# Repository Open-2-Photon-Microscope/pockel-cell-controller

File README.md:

# Pockel cell controller

An open source circuit to modulate laser intensity in a 2 Photon microscope. This modulation is necessary when visual stimulation is used to elicit responses from biological tissue (photoreceptors). The laser power is tunned high and low periodically (in our systems at 500Hz using a square wavefom at 80% duty cycle). When laser power is low, visual stimulation is on, when laser power is high, visual stimulation is off. 

This driver was built to control a laser modulator from Conoptics. Specifically [his model](https://www.lambdaphoto.co.uk/electro-optic-modulator-systems.html).

The main purpose of this circuit is to condition an analog signal using an fast switch IC that opens and closes the analog line using a digital 0-5V square signal (0V circuit open, 5V circuit closed). The original switching signal is 1.6ms at 5V and 0.4ms at 0V (composing a 500Hz signal), but other signals can be used.

This board can take an internal analog signal, where the signal amplitude (and therefore the laser intensity) is set by a potentiometer, or an external signal connected via a BNC cable.
 
The Pockels' cell driver was inspired by earlier devices designed and built by R. Berndt ([HIH Tübingen](<https://www.hih-tuebingen.de/en/>)), part of a project of [T. Euler's lab](<http://www.eye-tuebingen.de/eulerlab/>).

## To do:
1. Link board to KitSpace

## History:

v2.0
- Document, add licenses to the repository (A. Maia Chagas)
- KiCad designs updated to KiCad 5 (A. Maia Chagas)
- Designs of the board updated; ported to KiCad (F. Janiak)

V1.0
 - Pockels' cell driver design by R. Berndt ([HIH Tübingen](<https://www.hih-tuebingen.de/en/>)) and [T. Euler's lab](<http://www.eye-tuebingen.de/eulerlab/>).

--- 

Footprints for KiCad downloaded from [ultralibrarian](<https://app.ultralibrarian.com>).

- [CA3240](<https://app.ultralibrarian.com/details/f0fe15b2-106c-11e9-ab3a-0a3560a4cccc/Intersil/CA3240AE?uid=155cdc561030ca9b&exports=KiCAD>)
- [LM10CLN](<https://app.ultralibrarian.com/details/49f2f7e6-1073-11e9-ab3a-0a3560a4cccc/Texas-Instruments/LM10CLN?uid=6d97a49d38e0b250&exports=KiCAD>)

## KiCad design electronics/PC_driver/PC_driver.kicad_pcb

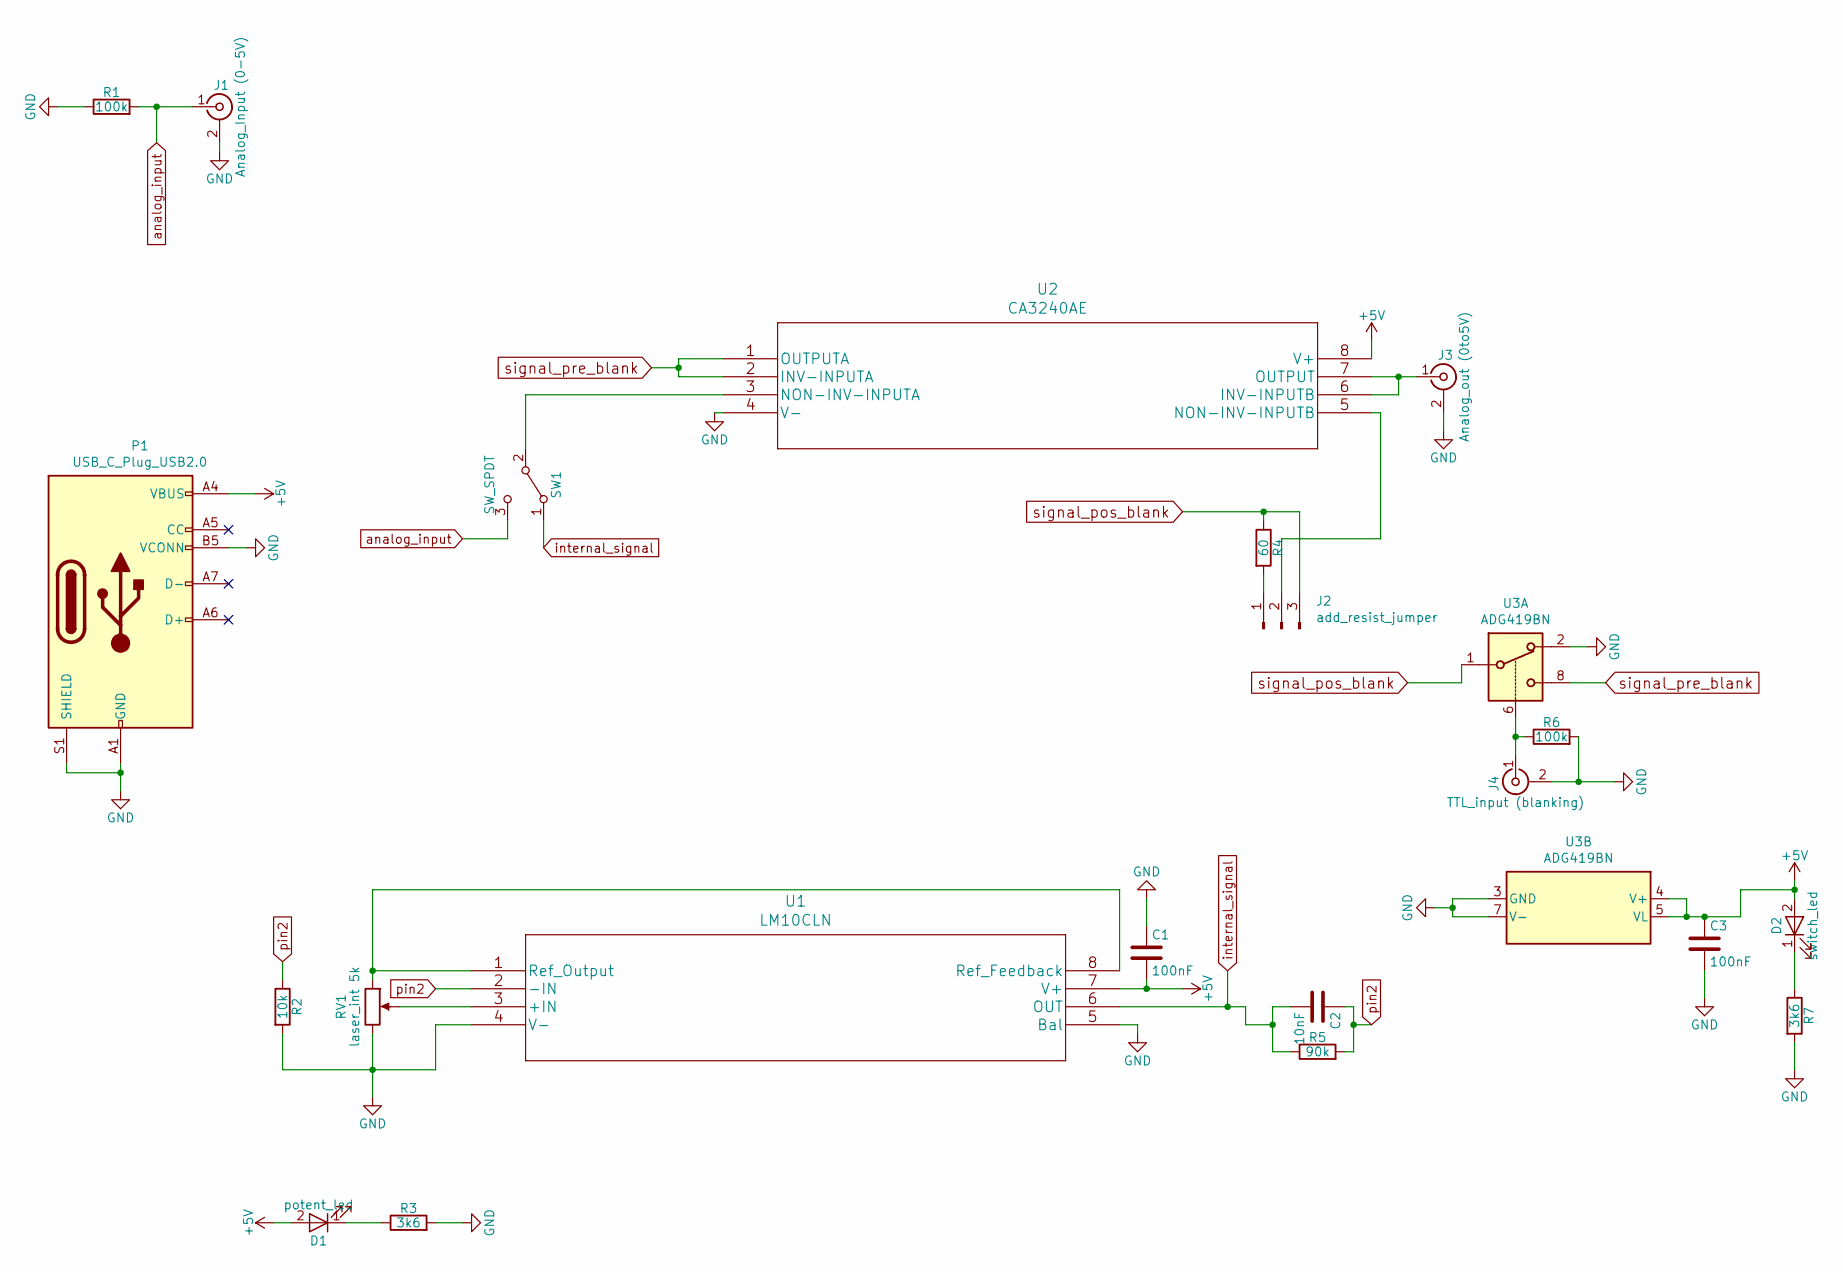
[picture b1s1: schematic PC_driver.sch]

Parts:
C1, C3: 100nF; C_Disc_D5.0mm_W2.5mm_P2.50mm
C2: 10nF; C_Disc_D5.0mm_W2.5mm_P2.50mm
D1: potent_led; LED_D5.0mm_Clear
D2: switch_led; LED_D5.0mm_Clear
J1: Analog_Input (0-5V); BNC_Amphenol_B6252HB-NPP3G-50_Horizontal
J2: add_resist_jumper; PinHeader_1x03_P2.54mm_Vertical
J3: Analog_out (0to5V); BNC_Amphenol_B6252HB-NPP3G-50_Horizontal
J4: TTL_input (blanking); BNC_Amphenol_B6252HB-NPP3G-50_Horizontal
P1: USB_C_Plug_USB2.0; USB_C_Receptacle_GCT_USB4085
R1, R6: 100k; R_Axial_DIN0309_L9.0mm_D3.2mm_P12.70mm_Horizontal
R2: 10k; R_Axial_DIN0309_L9.0mm_D3.2mm_P12.70mm_Horizontal
R3, R7: 3k6; R_Axial_DIN0309_L9.0mm_D3.2mm_P12.70mm_Horizontal
R4: 60; R_Axial_DIN0309_L9.0mm_D3.2mm_P12.70mm_Horizontal
R5: 90k; R_Axial_DIN0309_L9.0mm_D3.2mm_P12.70mm_Horizontal
RV1: laser_int 5k; Potentiometer_ACP_CA14-H5_Horizontal
SW1: SW_SPDT; SW_E-Switch_EG1224_SPDT_Angled
U1: LM10CLN; DIP-8_W7.62mm
U2: CA3240AE; DIP-8_W7.62mm
U3: ADG419BN; DIP-8_W7.62mm

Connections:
+5V: C1.2, C3.1, D1.2 (A), D2.2 (A), P1.A4 (VBUS), P1.A9 (VBUS), P1.B4 (VBUS), P1.B9 (VBUS), U1.7 (V+), U2.8 (V+), U3.4 (V+), U3.5 (VL)
GND: C1.1, C3.2, J1.2 (Ext), J3.2 (Ext), J4.2 (Ext), P1.A1 (GND), P1.A12 (GND), P1.B1 (GND), P1.B5 (VCONN), P1.B12 (GND), P1.S1 (SHIELD), R1.1, R2.2, R3.2, R6.2, R7.2, RV1.3, U1.4 (V-), U1.5 (Bal), U2.4 (V-), U3.2, U3.3 (GND), U3.7 (V-)
unnamed: D1.1 (K), R3.1
unnamed: D2.1 (K), R7.1
unnamed: J2.1, R4.2
unnamed: J2.2, U2.5 (NON-INV-INPUTB)
unnamed: J3.1 (In), U2.6 (INV-INPUTB), U2.7 (OUTPUT)
unnamed: J4.1 (In), R6.1, U3.6
unnamed: RV1.1, U1.1 (Ref_Output), U1.8 (Ref_Feedback)
unnamed: RV1.2, U1.3 (+IN)
unnamed: SW1.2 (B), U2.3 (NON-INV-INPUTA)
analog_input: J1.1 (In), R1.2, SW1.3 (C)
internal_signal: C2.2, R5.1, SW1.1 (A), U1.6 (OUT)
pin2: C2.1, R2.1, R5.2, U1.2 (-IN)
signal_pos_blank: J2.3, R4.1, U3.1
signal_pre_blank: U2.1 (OUTPUTA), U2.2 (INV-INPUTA), U3.8

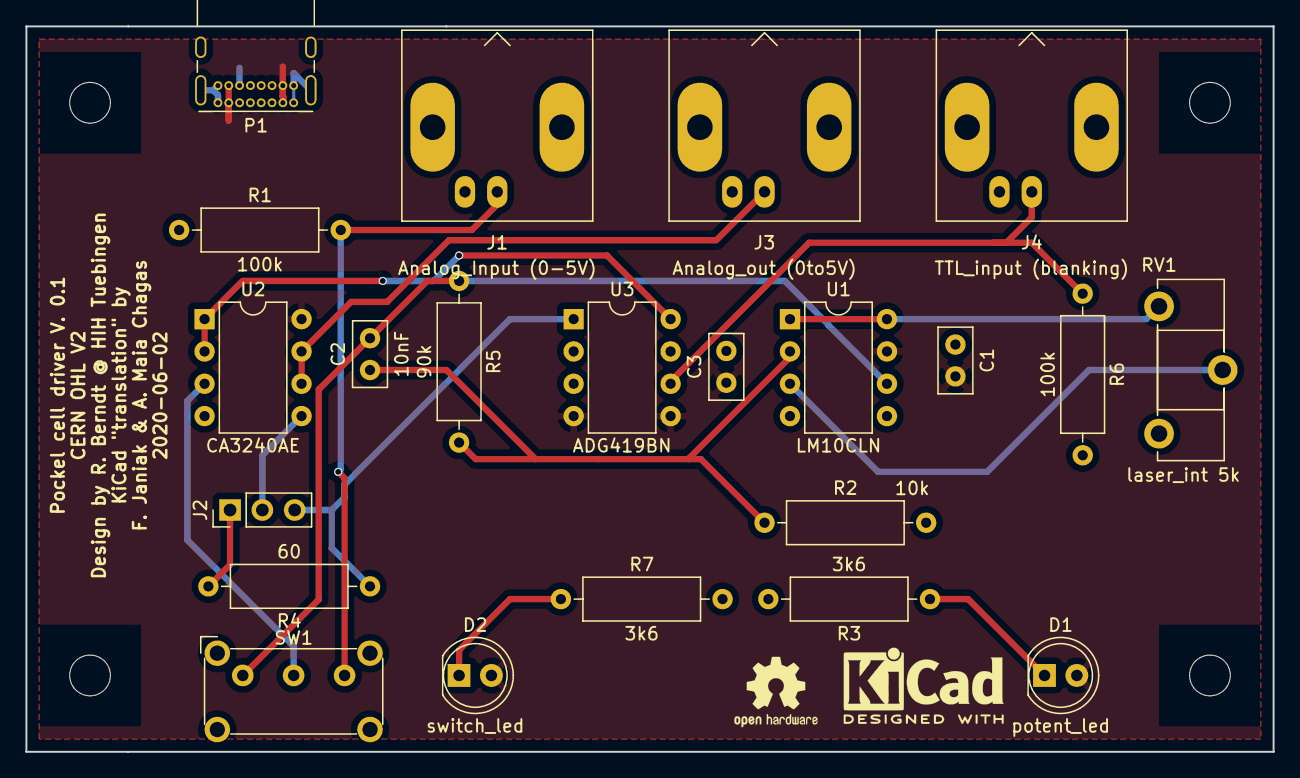
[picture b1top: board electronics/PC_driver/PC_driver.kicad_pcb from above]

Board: 2 copper layers, 98.0 x 57.0 mm, 22 parts (0 on the bottom side), 16 nets.

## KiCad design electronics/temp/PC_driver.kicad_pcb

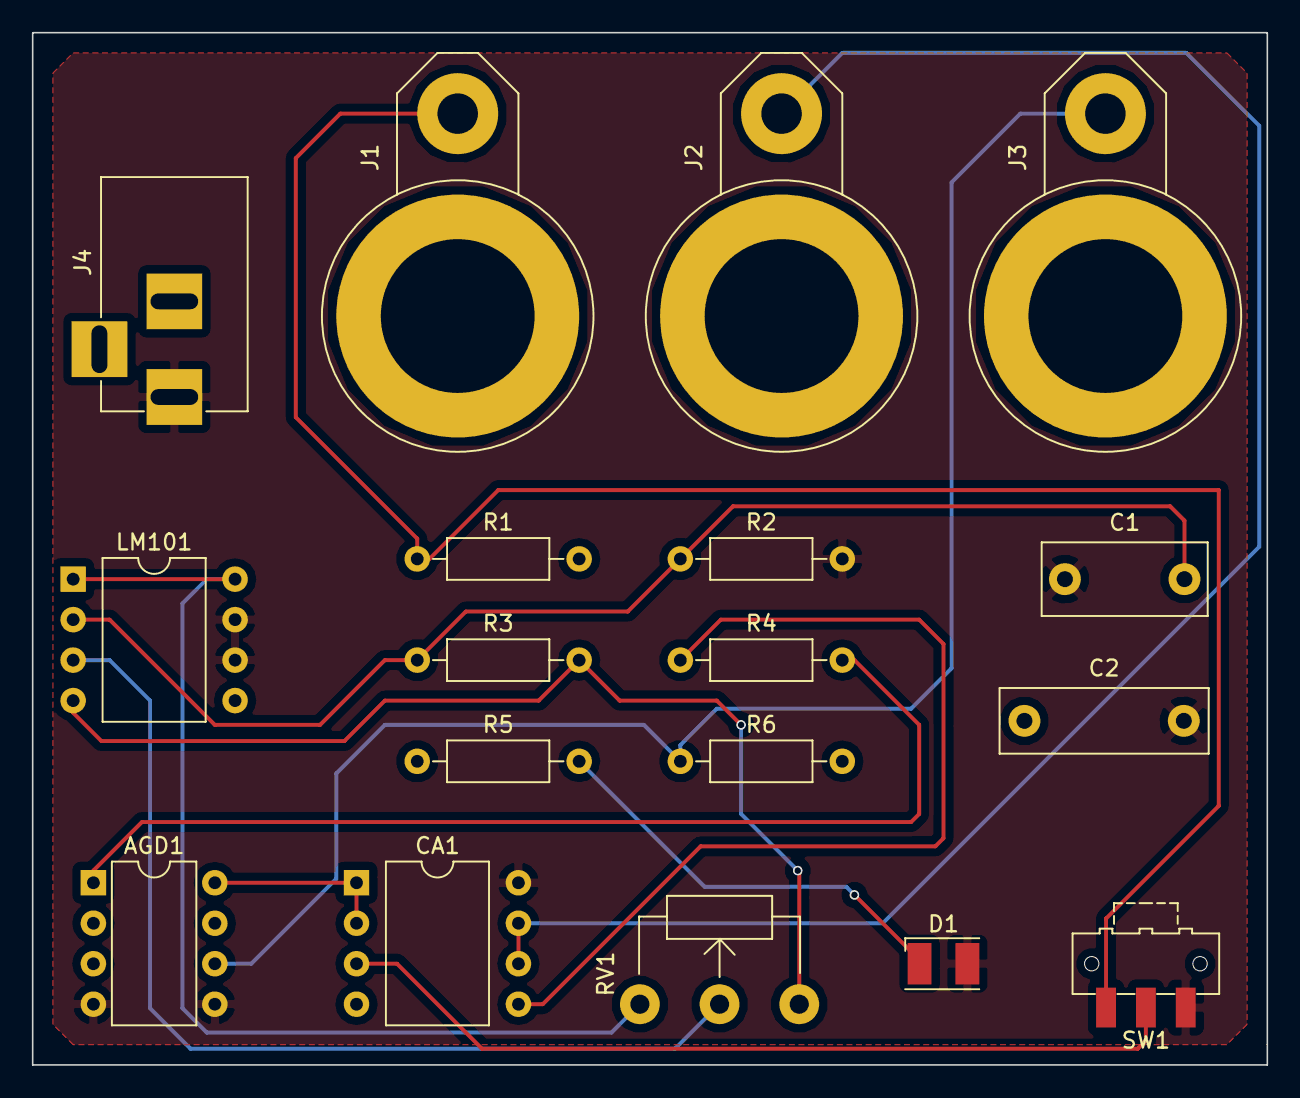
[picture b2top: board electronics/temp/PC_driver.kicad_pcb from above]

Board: 2 copper layers, 77.5 x 64.8 mm, 18 parts (0 on the bottom side), 14 nets.

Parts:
AGD1: AGD419BN2; DIP-8_W7.62mm
C1: 10nF; C_Rect_L10.3mm_W4.5mm_P7.50mm_MKS4
C2: 100nF; C_Rect_L13.0mm_W4.0mm_P10.00mm_FKS3_FKP3_MKS4
CA1: CA3240; DIP-8_W10.16mm
D1: LED; LED_PLCC-2
J1: Analog PC INP; BNC
J2: Analog OUT; BNC
J3: TTL INP; BNC
J4: Jack-DC; BARREL_JACK
LM101: LM10CLN; DIP-8_W10.16mm
R1, R6: 100k; R_Axial_DIN0207_L6.3mm_D2.5mm_P10.16mm_Horizontal
R2: 90k; R_Axial_DIN0207_L6.3mm_D2.5mm_P10.16mm_Horizontal
R3: 10k; R_Axial_DIN0207_L6.3mm_D2.5mm_P10.16mm_Horizontal
R4: 60; R_Axial_DIN0207_L6.3mm_D2.5mm_P10.16mm_Horizontal
R5: 3k6; R_Axial_DIN0207_L6.3mm_D2.5mm_P10.16mm_Horizontal
RV1: POT; Potentiometer_WirePads
SW1: SW_SPDT; SW_SPDT_CK-JS102011SAQN

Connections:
+5V: AGD1.4, AGD1.5, C1.1, C2.2, CA1.8, D1.2, J4.1, LM101.6, LM101.7, R2.2, SW1.1
D: AGD1.1, R4.2
GND: AGD1.2, AGD1.3, AGD1.7, C2.1, CA1.4, J4.2, J4.3, R1.2, R5.1, R6.2
unnamed: AGD1.6, J3.1, R6.1
unnamed: CA1.3, SW1.2
unnamed: CA1.5, R4.1
unnamed: CA1.6, CA1.7, J2.1
unnamed: D1.1, R5.2
unnamed: J1.1, R1.1, SW1.3
unnamed: LM101.1, LM101.8, RV1.1
unnamed: LM101.3, RV1.2
unnamed: LM101.4, R3.2, RV1.3
S2: AGD1.8, CA1.1, CA1.2
w2: C1.2, LM101.2, R2.1, R3.1

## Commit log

2020-03-06 filip's first implementation using KiCad4
2020-03-06 restart, some parts are available in kicad 5
2020-03-06 update components
2020-06-01 update board
2020-06-01 fix labels and buggy resistor
2020-06-01 finished schmatics and footprint association
2020-06-02 finish part placement, wiring and plotting
2020-06-02 correct misspelling
2020-06-09 correct bug on board plotting
2020-06-09 update readme with details of the laser modulator being used
2021-11-29 update media files and readme

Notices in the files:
electronics/PC_driver/PC_driver.kicad_pcb:
CERN OHL V2
